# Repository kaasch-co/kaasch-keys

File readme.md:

# The Kaasch Keys Keyboard
Is a keyboard idea I've had for a while. It's not supposed be seen a product, or as competing with other established open source keyboards. But a project of learning and nerding out about the gear of which we primarily communicate with computers.

## The (simple) spec
- A somewhat ergonomic keyboard split keyboard
- Suitable for gaming, which means space for dedicated modifier keys and number keys.
- Suitable for programming and general productivity, which means it needs to be comfortable during sustained use.

### The hardware
    MCU     = nRF52840          # widely supported, modern features, boards cheap on bulk
    SWITCH  = Cherry MX         # Favorite key and shows kindness to enthusiastic use.
    CASE    = Custom 3d print   # At least I'll be the one at fault for bad design.
    PLATE   = Custom 3d print   # Same as above.
    PCB     = Custom PCB        # Made in KiCad. Has gerber and keyboard plugin support.

### The software
With a nRF52840 board, ZMK or BlueMicro should be viable firmware to drive the keyboard, and offer plenty of customizability for my taste.
I'll also be free of fixing software problems years in the future, should I still wish to use the keyboard.

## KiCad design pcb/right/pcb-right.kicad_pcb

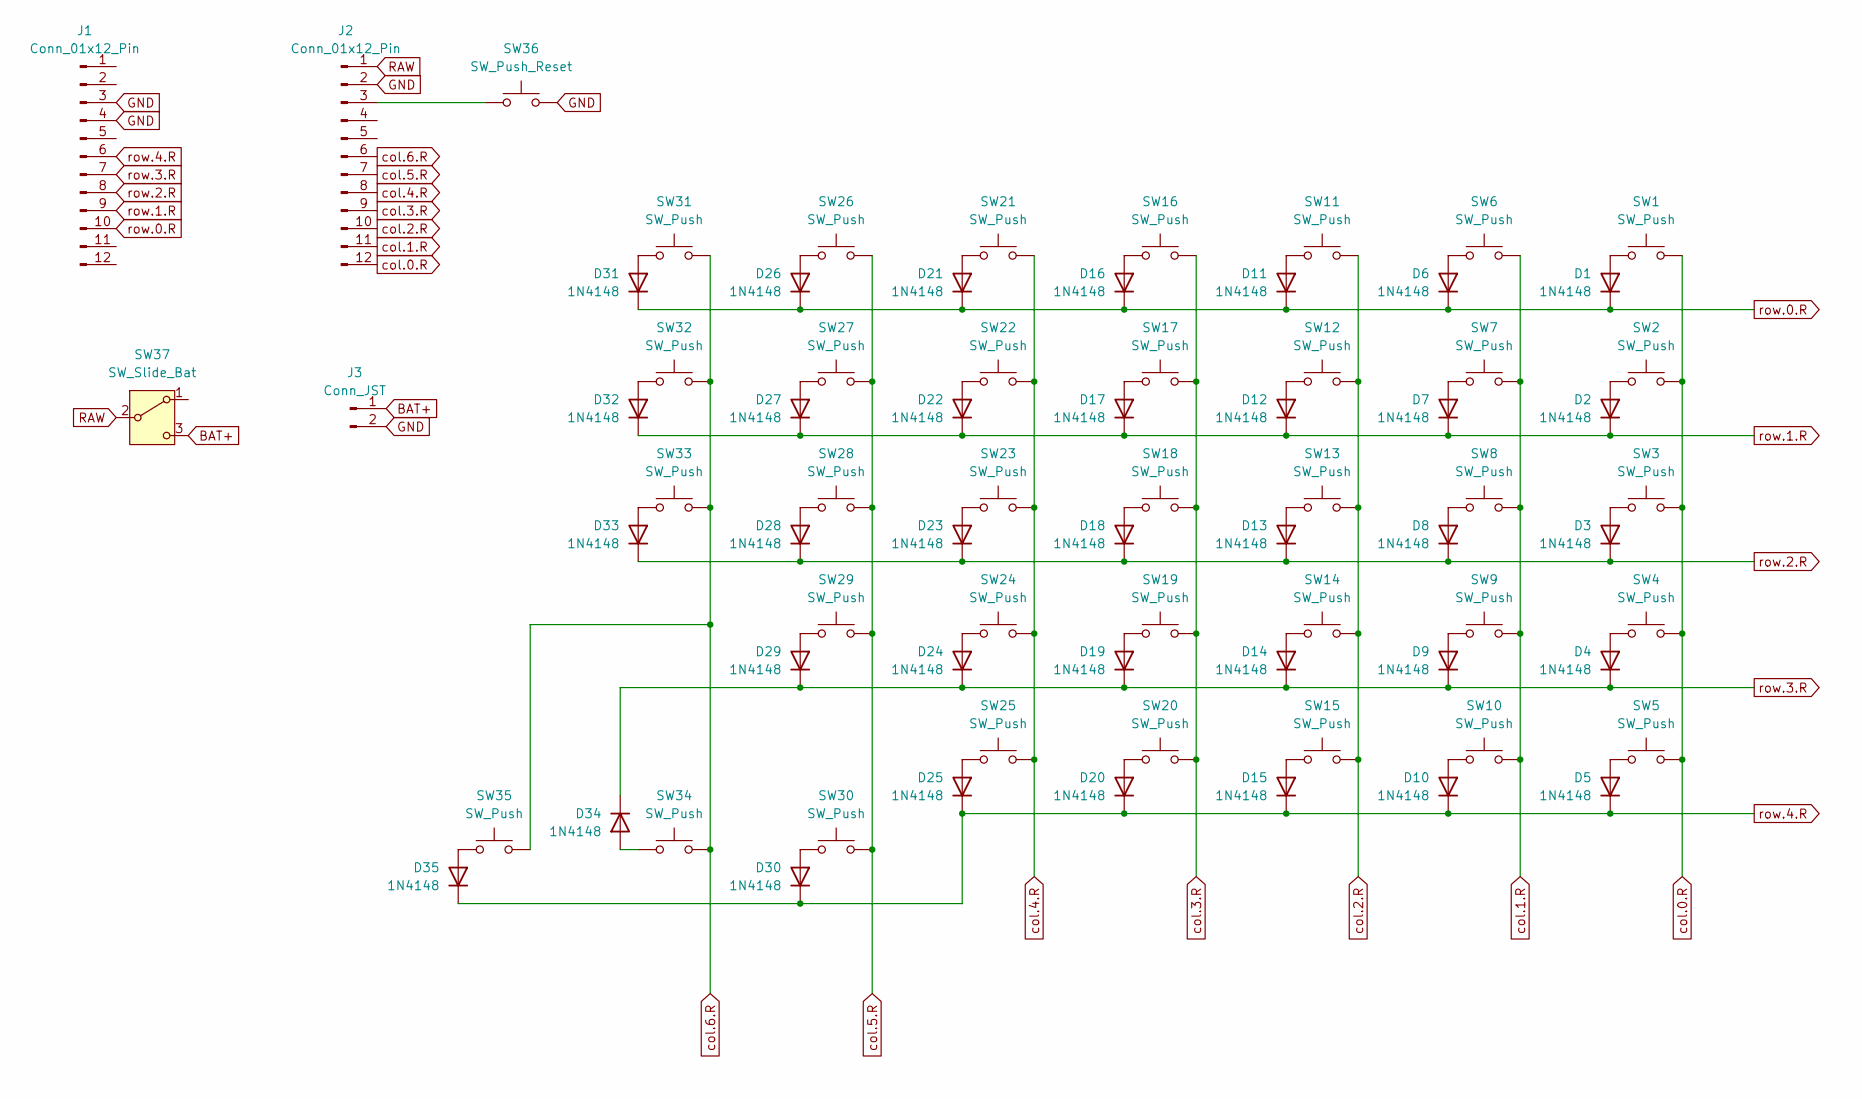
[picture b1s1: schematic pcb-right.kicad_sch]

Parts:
D1, D2, D3, D4, D5, D6, D7, D8, D9, D10, D11, D12, D13, D14, D15, D16, D17, D18, D19, D20, D21, D22, D23, D24, D25, D26, D27, D28, D29, D30, D31, D32, D33, D34, D35: 1N4148; D_1206_3216Metric
J1, J2: Conn_01x12_Pin; PinSocket_1x12_P2.54mm_Vertical
J3: Conn_JST; JST_PH_S2B-PH-K_1x02_P2.00mm_Horizontal
SW1, SW2, SW3, SW5, SW6, SW7, SW8, SW9, SW11, SW12, SW13, SW14, SW15, SW16, SW17, SW18, SW19, SW20, SW21, SW22, SW23, SW24, SW25, SW26, SW27, SW28, SW29, SW30, SW31, SW32, SW33, SW34, SW35: SW_Push; SW_Cherry_MX_1.00u_PCB
SW4, SW10: SW_Push; SW_Cherry_MX_1.50u_PCB
SW36: SW_Push_Reset; SW_SPST_B3U-1000P
SW37: SW_Slide_Bat; SW_SPDT_PCM12

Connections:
BAT+: J3.1, SW37.3 (C)
GND: J1.3, J1.4, J2.2, J3.2, SW36.2
unnamed: D1.2 (A), SW1.2
unnamed: D2.2 (A), SW2.2
unnamed: D3.2 (A), SW3.2
unnamed: D4.2 (A), SW4.2
unnamed: D5.2 (A), SW5.2
unnamed: D6.2 (A), SW6.2
unnamed: D7.2 (A), SW7.2
unnamed: D8.2 (A), SW8.2
unnamed: D9.2 (A), SW9.2
unnamed: D10.2 (A), SW10.2
unnamed: D11.2 (A), SW11.2
unnamed: D12.2 (A), SW12.2
unnamed: D13.2 (A), SW13.2
unnamed: D14.2 (A), SW14.2
unnamed: D15.2 (A), SW15.2
unnamed: D16.2 (A), SW16.2
unnamed: D17.2 (A), SW17.2
unnamed: D18.2 (A), SW18.2
unnamed: D19.2 (A), SW19.2
unnamed: D20.2 (A), SW20.2
unnamed: D21.2 (A), SW21.2
unnamed: D22.2 (A), SW22.2
unnamed: D23.2 (A), SW23.2
unnamed: D24.2 (A), SW24.2
unnamed: D25.2 (A), SW25.2
unnamed: D26.2 (A), SW26.2
unnamed: D27.2 (A), SW27.2
unnamed: D28.2 (A), SW28.2
unnamed: D29.2 (A), SW29.2
unnamed: D30.2 (A), SW30.2
unnamed: D31.2 (A), SW31.2
unnamed: D32.2 (A), SW32.2
unnamed: D33.2 (A), SW33.2
unnamed: D34.2 (A), SW34.2
unnamed: D35.2 (A), SW35.2
unnamed: J2.3, SW36.1
RAW: J2.1, SW37.2 (B)
col.0.R: J2.12, SW1.1, SW2.1, SW3.1, SW4.1, SW5.1
col.1.R: J2.11, SW6.1, SW7.1, SW8.1, SW9.1, SW10.1
col.2.R: J2.10, SW11.1, SW12.1, SW13.1, SW14.1, SW15.1
col.3.R: J2.9, SW16.1, SW17.1, SW18.1, SW19.1, SW20.1
col.4.R: J2.8, SW21.1, SW22.1, SW23.1, SW24.1, SW25.1
col.5.R: J2.7, SW26.1, SW27.1, SW28.1, SW29.1, SW30.1
col.6.R: J2.6, SW31.1, SW32.1, SW33.1, SW34.1, SW35.1
row.0.R: D1.1 (K), D6.1 (K), D11.1 (K), D16.1 (K), D21.1 (K), D26.1 (K), D31.1 (K), J1.10
row.1.R: D2.1 (K), D7.1 (K), D12.1 (K), D17.1 (K), D22.1 (K), D27.1 (K), D32.1 (K), J1.9
row.2.R: D3.1 (K), D8.1 (K), D13.1 (K), D18.1 (K), D23.1 (K), D28.1 (K), D33.1 (K), J1.8
row.3.R: D4.1 (K), D9.1 (K), D14.1 (K), D19.1 (K), D24.1 (K), D29.1 (K), D34.1 (K), J1.7
row.4.R: D5.1 (K), D10.1 (K), D15.1 (K), D20.1 (K), D25.1 (K), D30.1 (K), D35.1 (K), J1.6

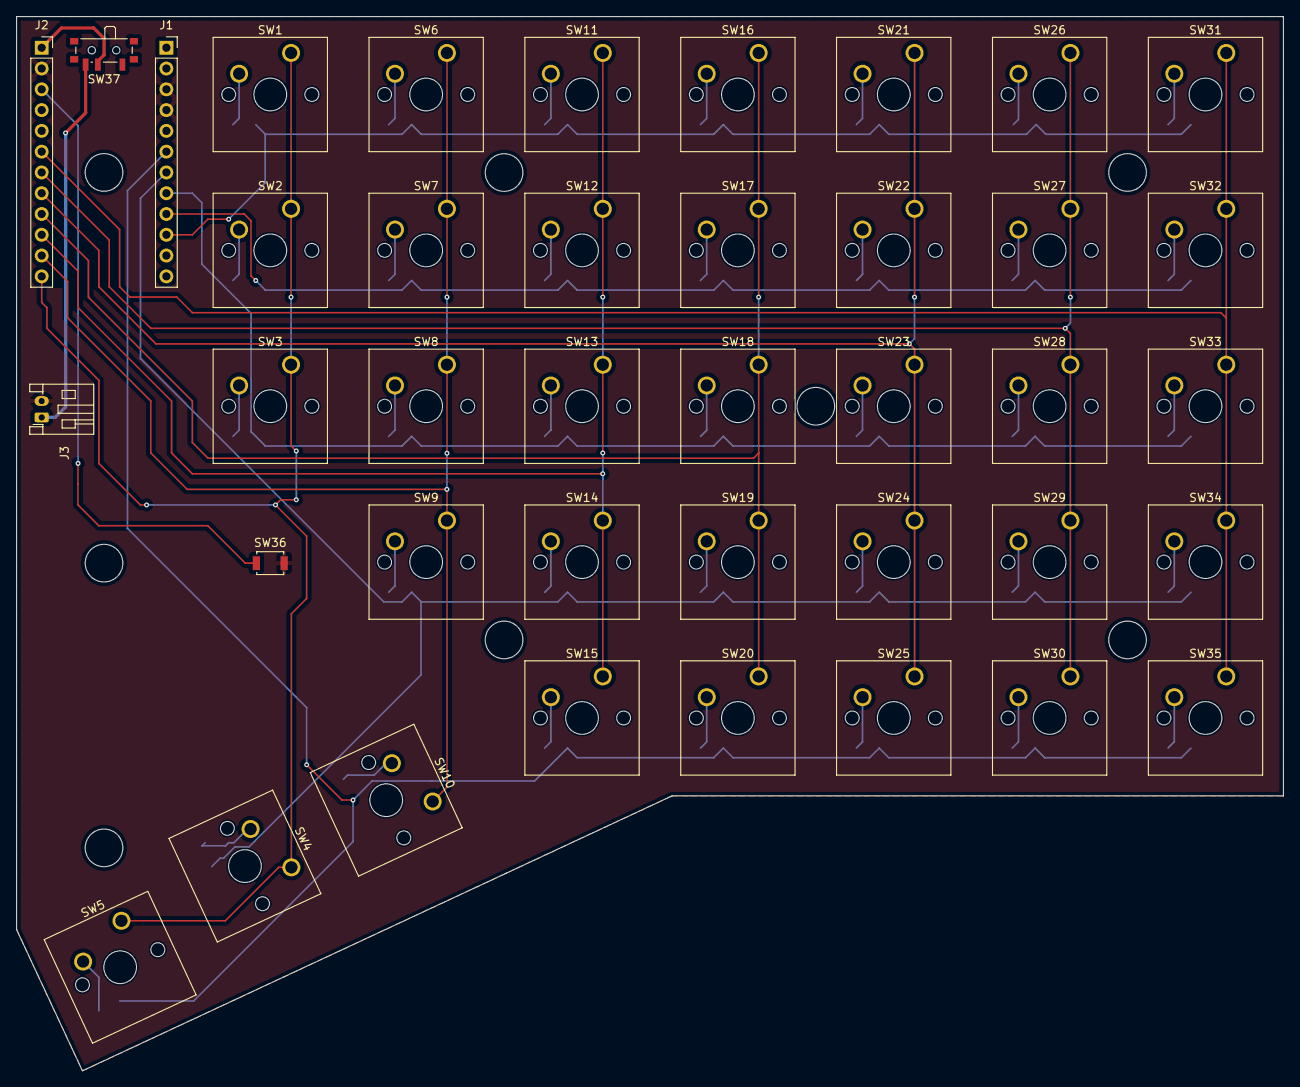
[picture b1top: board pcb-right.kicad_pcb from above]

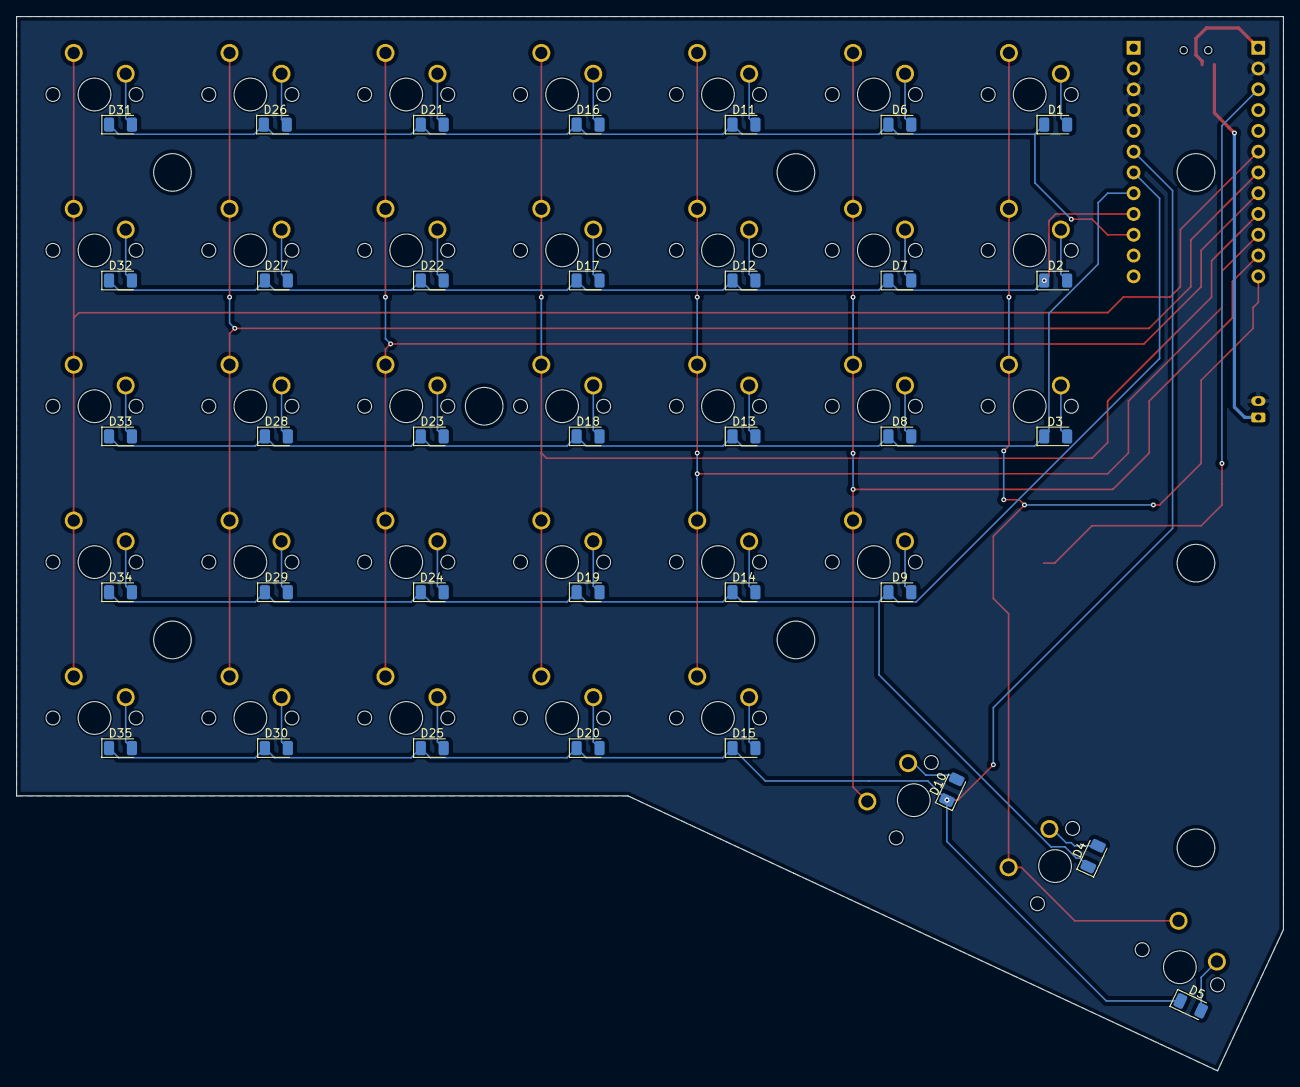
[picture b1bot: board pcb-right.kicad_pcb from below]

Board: 2 copper layers, 154.8 x 128.9 mm, 75 parts (35 on the bottom side), 51 nets.

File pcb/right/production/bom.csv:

Designator,Footprint,Quantity,Value,LCSC Part #
"D1, D10, D11, D12, D13, D14, D15, D16, D17, D18, D19, D2, D20, D21, D22, D23, D24, D25, D26, D27, D28, D29, D3, D30, D31, D32, D33, D34, D35, D4, D5, D6, D7, D8, D9",1206,35,1N4148,
"J1, J2",PinSocket_1x12_P2.54mm_Vertical,2,Conn_01x12_Pin,
J3,JST_PH_S2B-PH-K_1x02_P2.00mm_Horizontal,1,Conn_JST,
"SW1, SW11, SW12, SW13, SW14, SW15, SW16, SW17, SW18, SW19, SW2, SW20, SW21, SW22, SW23, SW24, SW25, SW26, SW27, SW28, SW29, SW3, SW30, SW31, SW32, SW33, SW34, SW35, SW5, SW6, SW7, SW8, SW9",SW_Cherry_MX_1.00u_PCB,33,SW_Push,
"SW10, SW4",SW_Cherry_MX_1.50u_PCB,2,SW_Push,
SW36,SW_SPST_B3U-1000P,1,SW_Push_Reset,
SW37,SW_SPDT_PCM12,1,SW_Slide_Bat,

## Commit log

2025-10-27 added readme
2025-10-28 cad files
2025-10-29 lets goo
2025-10-29 Update hardware and software details in README
2025-10-29 Refine hardware section in readme.md
    Updated hardware specifications for clarity and conciseness.
2025-10-29 gitignores and stuff
2025-10-30 fixes
2025-10-31 new naming and shit, big steps on left pcb
2025-11-01 left pcb complete and ready for testing
2025-11-02 updated column widths
2025-11-03 alternative thumb cluster position
2025-11-04 finished new layout
2025-11-06 iterations
2025-11-06 more work on l2
2025-11-07 swaggers
2025-11-09 continue on design
2025-11-10 gerberz for testing export config, ready for 3d print testing
2025-11-10 moore
2025-11-10 cleanup
2025-11-11 fab prep
2025-11-11 prod files - but need to fix JST connector type to PH
2025-11-12 pcb corrections
2025-11-14 changes 2
2025-11-16 added stls
